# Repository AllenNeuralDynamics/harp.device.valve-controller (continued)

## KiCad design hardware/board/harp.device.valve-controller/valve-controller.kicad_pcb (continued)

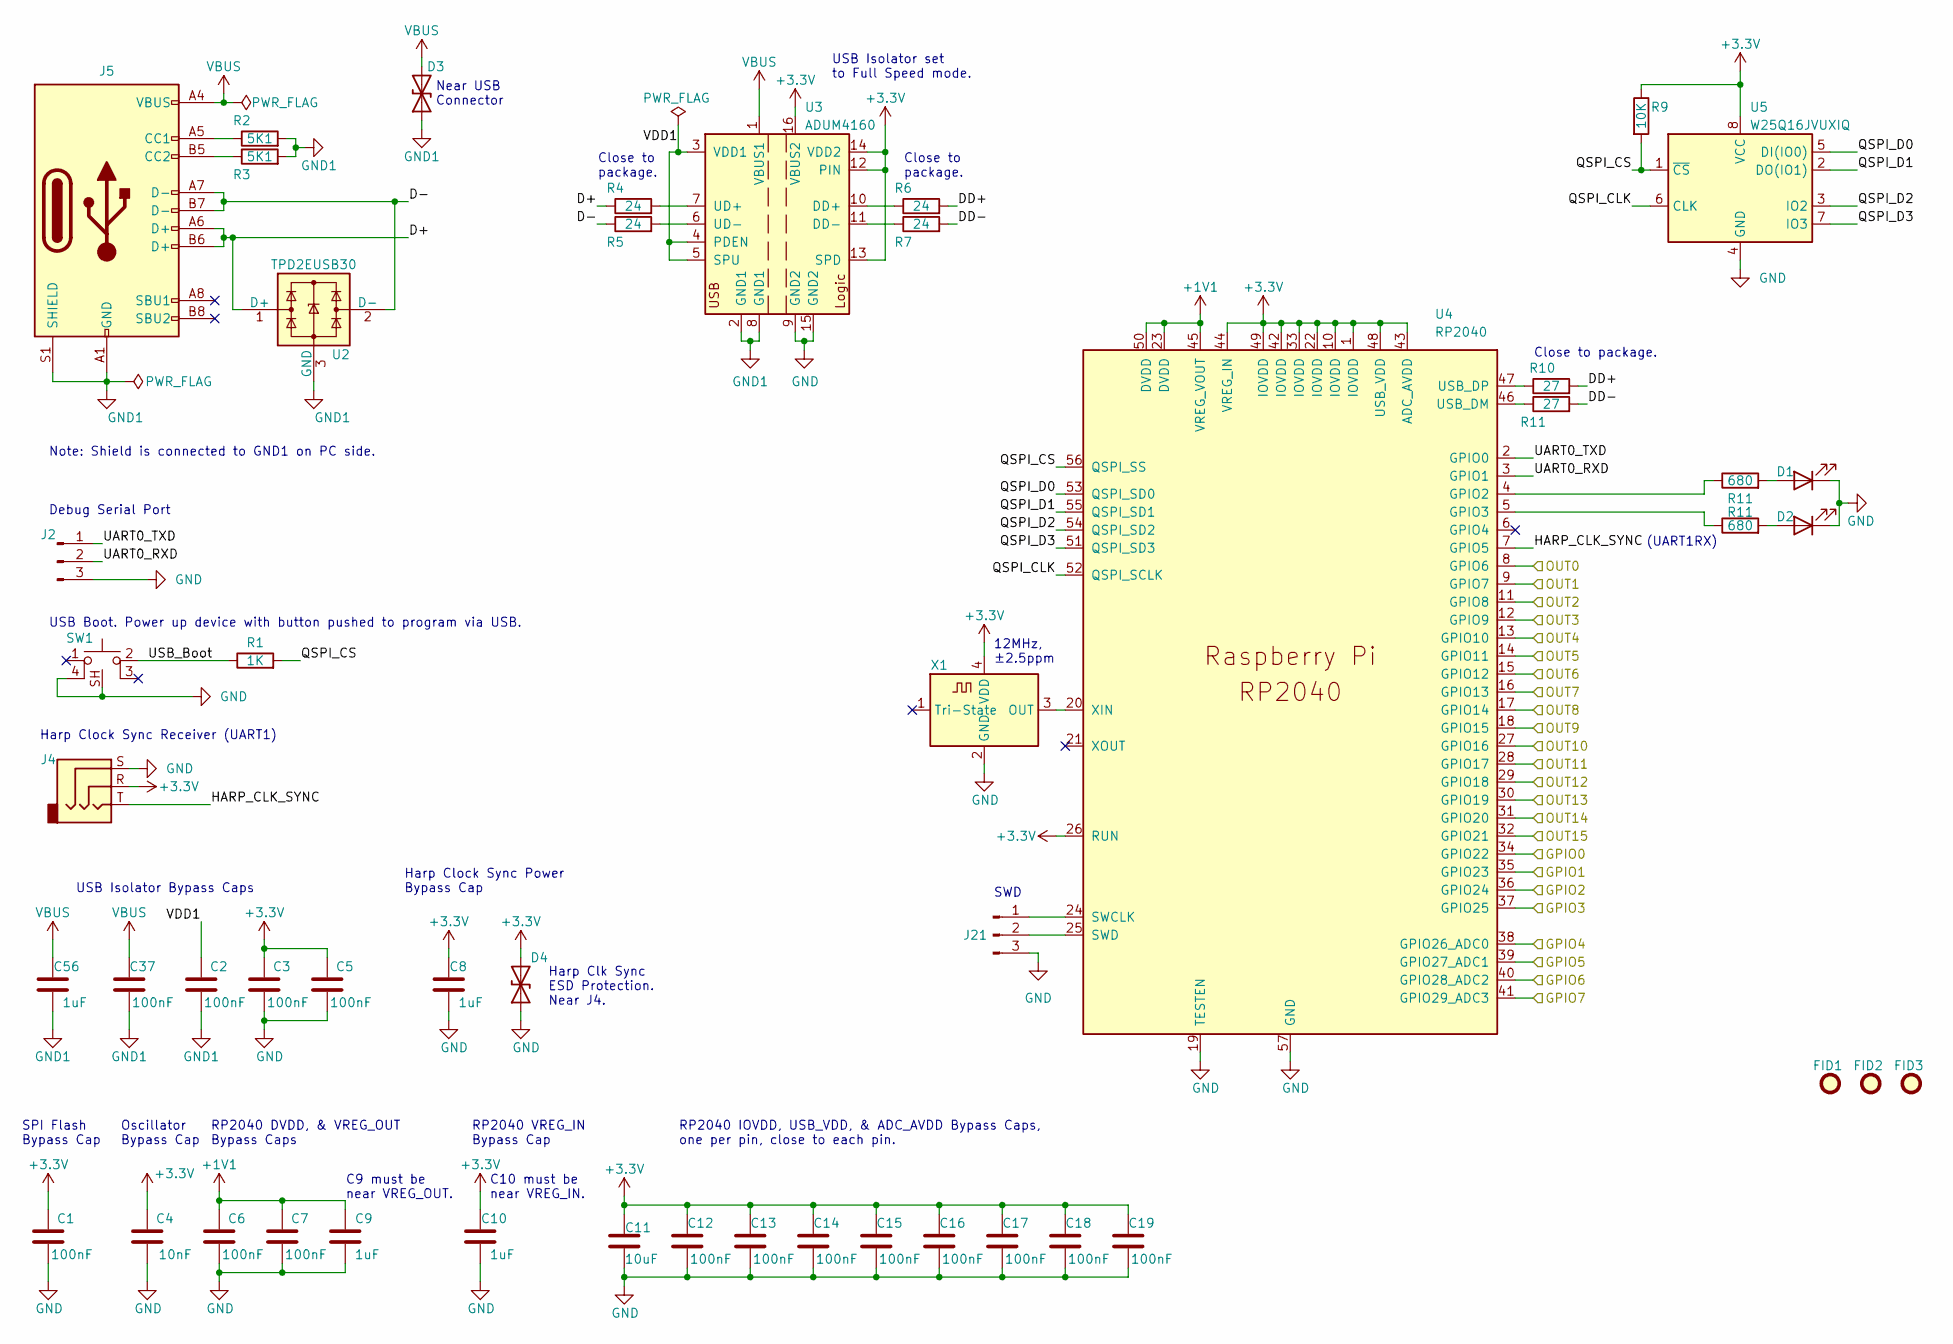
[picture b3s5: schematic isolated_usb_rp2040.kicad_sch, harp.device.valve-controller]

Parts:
C1, C2, C3, C5, C6, C7, C12, C13, C14, C15, C16, C17, C18, C19, C37: 100nF; C_0402_1005Metric; Rated Voltage 50V; Tolerance 10%
C4: 10nF; C_0402_1005Metric; Rated Voltage 25V; Tolerance 10%
C8, C9, C10, C56: 1uF; C_0402_1005Metric; Rated Voltage 35V
C11: 10uF; C_0805_2012Metric
D1, D2: LED; LED_0603_1608Metric_Pad1.05x0.95mm_HandSolder
D3, D4: D_TVS; D_0402_1005Metric
FID1, FID2, FID3: Fiducial; Fiducial_0.5mm_Mask1mm
J2, J21: Conn_01x03_Male; PinHeader_1x03_P2.54mm_Vertical
J4: AudioJack3; Jack_3.5mm_CUI_SJ-3524-SMT_Horizontal
J5: USB_C_Receptacle_USB2.0; USB_C_Receptacle_JAE_DX07S016JA1R1500
R1: 1K; R_0402_1005Metric; Tolerance 1%
R2, R3: 5K1; R_0402_1005Metric; Tolerance 1%
R4, R5, R6, R7: 24; R_0402_1005Metric; Tolerance 1%
R9: 10K; R_0402_1005Metric
R10, R11: 27; R_0402_1005Metric; Tolerance 1%
SW1: SW_Push_1P1T-SH_NO_Vertical_Wuerth_WS-TASV
U2: TPD2EUSB30; Texas_DRT-3
U3: ADUM4160; SOIC-16W_7.5x10.3mm_P1.27mm
U4: RP2040; RP2040-QFN-56
U5: W25Q16JVUXIQ; Winbond-8USON-2x3mm
X1: ECS-TXO-2016; Crystal_SMD_2016-4Pin_2.0x1.6mm; Tolerance ±2.5ppm

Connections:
+1V1: C6.2, C7.2, C9.1, U4.23 (DVDD), U4.45 (VREG_VOUT), U4.50 (DVDD)
+3.3V: C1.2, C3.2, C4.2, C5.2, C8.1, C10.1, C11.1, C12.2, C13.2, C14.2, C15.2, C16.2, C17.2, C18.2, C19.2, D4.2 (A2), J4.R, R9.1, U3.12 (PIN), U3.13 (SPD), U3.14 (VDD2), U3.16 (VBUS2), U4.1 (IOVDD), U4.10 (IOVDD), U4.22 (IOVDD), U4.26 (RUN), U4.33 (IOVDD), U4.42 (IOVDD), U4.43 (ADC_AVDD), U4.44 (VREG_IN), U4.48 (USB_VDD), U4.49 (IOVDD), U5.8 (VCC), X1.4 (VDD); also elsewhere on the board
/Harp Core RP2040 + Isolated USB/D+: J5.A6 (D+), J5.B6 (D+), R4.1, U2.1 (D+)
/Harp Core RP2040 + Isolated USB/D-: J5.A7 (D-), J5.B7 (D-), R5.1, U2.2 (D-)
/Harp Core RP2040 + Isolated USB/DD+: R6.2, R10.2
/Harp Core RP2040 + Isolated USB/GPIO0: U4.34 (GPIO22); also elsewhere on the board
/Harp Core RP2040 + Isolated USB/GPIO1: U4.35 (GPIO23); also elsewhere on the board
/Harp Core RP2040 + Isolated USB/GPIO2: U4.36 (GPIO24); also elsewhere on the board
/Harp Core RP2040 + Isolated USB/GPIO3: U4.37 (GPIO25); also elsewhere on the board
/Harp Core RP2040 + Isolated USB/GPIO4: U4.38 (GPIO26_ADC0); also elsewhere on the board
/Harp Core RP2040 + Isolated USB/GPIO5: U4.39 (GPIO27_ADC1); also elsewhere on the board
/Harp Core RP2040 + Isolated USB/GPIO6: U4.40 (GPIO28_ADC2); also elsewhere on the board
/Harp Core RP2040 + Isolated USB/GPIO7: U4.41 (GPIO29_ADC3); also elsewhere on the board
/Harp Core RP2040 + Isolated USB/HARP_CLK_SYNC: J4.T, U4.7 (GPIO5)
/Harp Core RP2040 + Isolated USB/OUT0: U4.8 (GPIO6); also elsewhere on the board
/Harp Core RP2040 + Isolated USB/OUT1: U4.9 (GPIO7); also elsewhere on the board
/Harp Core RP2040 + Isolated USB/OUT2: U4.11 (GPIO8); also elsewhere on the board
/Harp Core RP2040 + Isolated USB/OUT3: U4.12 (GPIO9); also elsewhere on the board
/Harp Core RP2040 + Isolated USB/OUT4: U4.13 (GPIO10); also elsewhere on the board
/Harp Core RP2040 + Isolated USB/OUT5: U4.14 (GPIO11); also elsewhere on the board
/Harp Core RP2040 + Isolated USB/OUT6: U4.15 (GPIO12); also elsewhere on the board
/Harp Core RP2040 + Isolated USB/OUT7: U4.16 (GPIO13); also elsewhere on the board
/Harp Core RP2040 + Isolated USB/OUT8: U4.17 (GPIO14); also elsewhere on the board
/Harp Core RP2040 + Isolated USB/OUT9: U4.18 (GPIO15); also elsewhere on the board
/Harp Core RP2040 + Isolated USB/OUT10: U4.27 (GPIO16); also elsewhere on the board
/Harp Core RP2040 + Isolated USB/OUT11: U4.28 (GPIO17); also elsewhere on the board
/Harp Core RP2040 + Isolated USB/OUT12: U4.29 (GPIO18); also elsewhere on the board
/Harp Core RP2040 + Isolated USB/OUT13: U4.30 (GPIO19); also elsewhere on the board
/Harp Core RP2040 + Isolated USB/OUT14: U4.31 (GPIO20); also elsewhere on the board
/Harp Core RP2040 + Isolated USB/OUT15: U4.32 (GPIO21); also elsewhere on the board
/Harp Core RP2040 + Isolated USB/QSPI_CLK: U4.52 (QSPI_SCLK), U5.6 (CLK)
/Harp Core RP2040 + Isolated USB/QSPI_CS: R1.2, R9.2, U4.56 (QSPI_SS), U5.1 (~CS)
/Harp Core RP2040 + Isolated USB/QSPI_D0: U4.53 (QSPI_SD0), U5.5 (DI(IO0))
/Harp Core RP2040 + Isolated USB/QSPI_D1: U4.55 (QSPI_SD1), U5.2 (DO(IO1))
/Harp Core RP2040 + Isolated USB/QSPI_D2: U4.54 (QSPI_SD2), U5.3 (IO2)
/Harp Core RP2040 + Isolated USB/QSPI_D3: U4.51 (QSPI_SD3), U5.7 (IO3)
/Harp Core RP2040 + Isolated USB/UART0_RXD: J2.2, U4.3 (GPIO1)
/Harp Core RP2040 + Isolated USB/UART0_TXD: J2.1, U4.2 (GPIO0)
/Harp Core RP2040 + Isolated USB/USB_Boot: R1.1, SW1.2
/Harp Core RP2040 + Isolated USB/VDD1: C2.2, U3.3 (VDD1), U3.4 (PDEN), U3.5 (SPU)
GND: C1.1, C3.1, C4.1, C5.1, C6.1, C7.1, C8.2, C9.2, C10.2, C11.2, C12.1, C13.1, C14.1, C15.1, C16.1, C17.1, C18.1, C19.1, D1.1 (K), D2.1 (K), D4.1 (A1), J2.3, J4.S, J21.3, SW1.4, SW1.SH, U3.9 (GND2), U3.15 (GND2), U4.19 (TESTEN), U4.57 (GND), U5.4 (GND), X1.2 (GND); also elsewhere on the board
GND1: C2.1, C37.1, C56.2, D3.1 (A1), J5.A1 (GND), J5.A12 (GND), J5.B1 (GND), J5.B12 (GND), J5.S1 (SHIELD), R2.2, R3.2, U2.3 (GND), U3.2 (GND1), U3.8 (GND1)
unnamed: J5.A5 (CC1), R2.1
unnamed: J5.B5 (CC2), R3.1
unnamed: J21.1, U4.24 (SWCLK)
unnamed: J21.2, U4.25 (SWD)
unnamed: R6.1, U3.10 (DD+)
unnamed: R7.1, U3.11 (DD-)
unnamed: R4.2, U3.7 (UD+)
unnamed: R5.2, U3.6 (UD-)
unnamed: R10.1, U4.47 (USB_DP)
unnamed: U4.20 (XIN), X1.3 (OUT)
VBUS: C37.2, C56.1, D3.2 (A2), J5.A4 (VBUS), J5.A9 (VBUS), J5.B4 (VBUS), J5.B9 (VBUS), U3.1 (VBUS1)

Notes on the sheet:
Close to package.
SWD
Near USB Connector
Close to package.
(UART1RX)
Harp Clk Sync ESD Protection. Near J4.
RP2040 VREG_IN Bypass Cap
Oscillator Bypass Cap
Harp Clock Sync Power Bypass Cap
C10 must be near VREG_IN.
RP2040 DVDD, & VREG_OUT Bypass Caps
Debug Serial Port
USB Boot. Power up device with button pushed to program via USB.
C9 must be near VREG_OUT.
Harp Clock Sync Receiver (UART1)
12MHz, ±2.5ppm
Note: Shield is connected to GND1 on PC side.
RP2040 IOVDD, USB_VDD, & ADC_AVDD Bypass Caps, one per pin, close to each pin.
USB Isolator Bypass Caps
SPI Flash Bypass Cap
USB Isolator set to Full Speed mode.

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
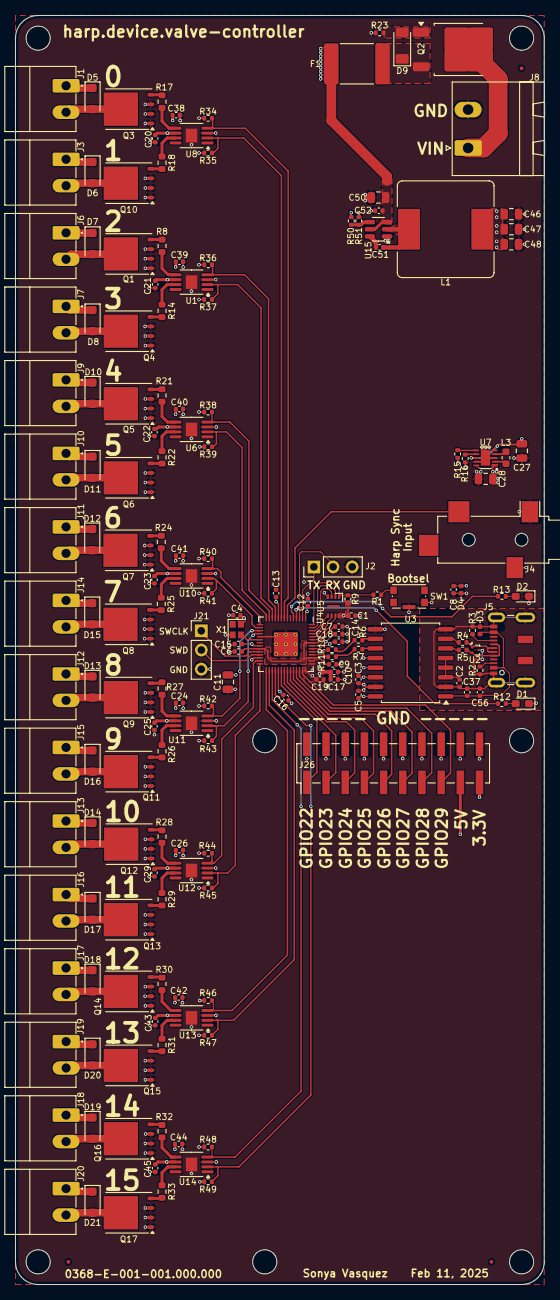
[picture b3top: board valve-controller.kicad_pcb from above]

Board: 4 copper layers, 70.0 x 168.0 mm, 177 parts (1 on the bottom side), 119 nets.

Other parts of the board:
R12, R13: 680; R_0402_1005Metric
REF1: OSHW-Logo2_7.3x6mm_SilkScreen

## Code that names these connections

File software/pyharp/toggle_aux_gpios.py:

#!/usr/bin/env python3
from pyharp.device import Device, DeviceMode
from pyharp.messages import HarpMessage
from pyharp.messages import MessageType
from app_registers import AppRegs
from struct import pack, unpack
from time import sleep
import os
import serial.tools.list_ports

# Open serial connection with the first Valve Controller.
com_port = None
ports = serial.tools.list_ports.comports()
for port, desc, hwid in sorted(ports):
    if desc.startswith("valve-controller"):
        print("{}: {} [{}]".format(port, desc, hwid))
        com_port = port
        break
device = Device(com_port)
device.info()                           # Display device's info on screen

print("Enabling AUX GPIOS: 0, 3, 4, 5, 6 as outputs")
gpio_dir = 0b01111001
reply = device.send(HarpMessage.WriteU8(AppRegs.AuxGPIODir, gpio_dir).frame)
print(f"reply: {reply.payload[0]:08b}")
print()
sleep(1.0)

GPIO_STATES = \
[
    (AppRegs.AuxGPIOSet, 0b00001001, "Setting GPIO0,3"),
    (AppRegs.AuxGPIOClear, 0b00001001, "Clearing GPIO0,3"),
    (AppRegs.AuxGPIOState, 0b00001001, "Setting GPIO0, 3 by writing to State"),
    (AppRegs.AuxGPIOState, 0b00000000, "Clearing GPIO0, 3 by writing to State"),
    (AppRegs.AuxGPIOState, 0b00010000, "Setting GPIO5 by writing to State"),
    (AppRegs.AuxGPIOState, 0b00100000, "Setting GPIO6 and Clearing 5 by writing to State"),
    (AppRegs.AuxGPIOState, 0b01000000, "Setting GPIO7 and Clearing 6 by writing to State"),
    (AppRegs.AuxGPIOState, 0b00000000, "Clearing all GPIOs"),
]

for reg, value , msg in GPIO_STATES:
    print(msg)
    reply = device.send(HarpMessage.WriteU8(reg, value).frame)
    print(f"reply: {reply.payload[0]:08b}")
    print()
    sleep(1.0)

# Close connection
device.disconnect()

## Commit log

2025-02-04 draft board layout
2025-02-06 route pcb
2025-02-07 update pcb power supply
2025-02-07 update bom
2025-02-09 prep hw initial release
2025-02-09 change usb descriptors
2025-02-11 add device.yaml and gpio pinout pic
2025-02-18 update silkscreen w/ gpio descriptions
2025-02-18 get boilerplate code compiling
2025-02-19 draft hit and hold valve driver
2025-02-20 draft hit and hold controller
2025-02-20 draft get/set valve config
2025-02-20 draft harp Reg access to config valve hit/hold settings
2025-02-20 attach bulk valve control registers to ValveDrivers
2025-02-20 tick ValveDriver FSMs in app update fn
2025-02-21 add demo scripts
2025-02-21 get hit and hold under harp control working
2025-02-21 draft aux gpio control
2025-02-22 test aux port; add pyharp test
2025-02-24 let AuxGPIO input change trigger EVENTS
2025-02-28 add mini clamp connector aux gpio breakout
2025-03-01 route breakout board layout partially
2025-03-03 update breakout
2025-03-07 update breakout board silk
2025-03-10 fix CMakeLists env variable
2025-03-10 update cmakelists
2025-03-10 update mini clamp breakout bom
2025-03-18 draft debouncing on aux inputs
2025-03-18 tease pwm class into its own repo
2025-09-09 disambiguate LEDs in schematic
2025-09-12 update MPN
